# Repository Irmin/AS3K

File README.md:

# The Mechanical AlphaSmart 3000
This is a hardware mod for the AlphaSmart 3000 that swaps the keyboard out for a mechanical one.

The revisions here have compatibility issues and are deprecated. Information on the most recent revision is available [here](https://tilde.club/~jy4m/alphasmart).

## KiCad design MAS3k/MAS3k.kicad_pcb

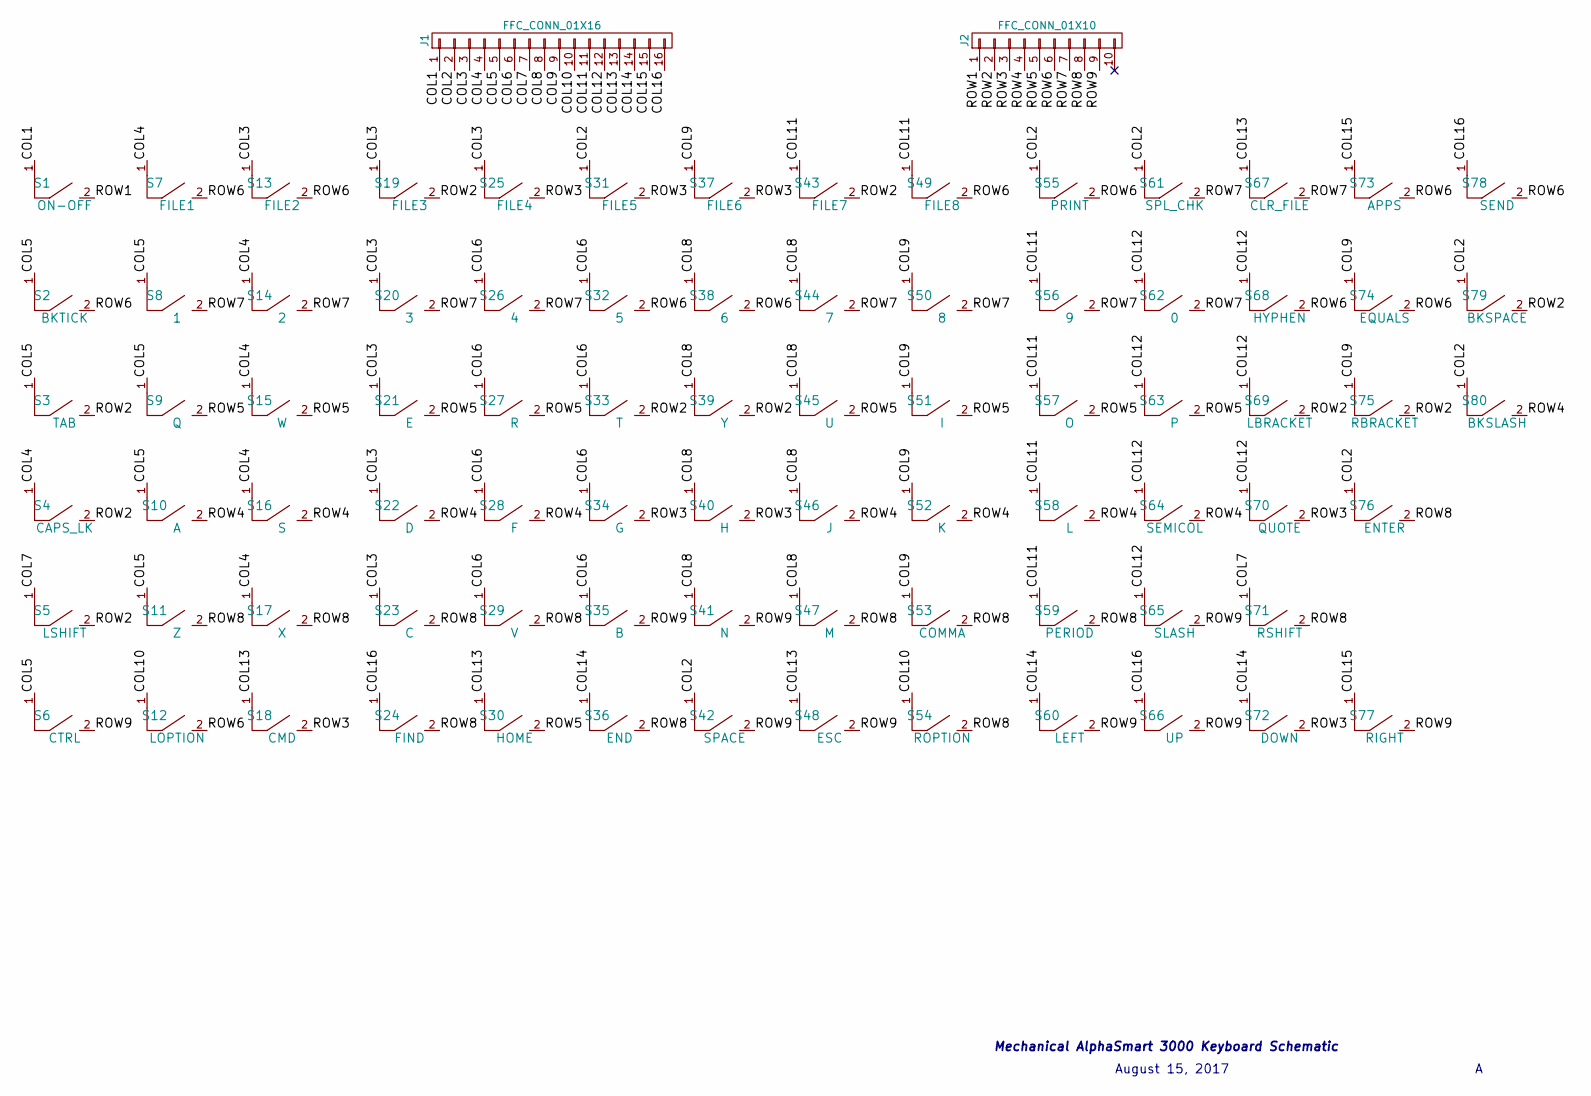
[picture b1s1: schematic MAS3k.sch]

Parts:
J1: FFC_CONN_01X16; SLW16R-1C7LF
J2: FFC_CONN_01X10; HLW10R-2C7LF
S1: ON-OFF; MX1A
S2: BKTICK; MX1A
S3: TAB; MX1A
S4: CAPS_LK; MX1A
S5: LSHIFT; MX1A
S6: CTRL; MX1A
S7: FILE1; MX1A
S8: 1; MX1A
S9: Q; MX1A
S10: A; MX1A
S11: Z; MX1A
S12: LOPTION; MX1A
S13: FILE2; MX1A
S14: 2; MX1A
S15: W; MX1A
S16: S; MX1A
S17: X; MX1A
S18: CMD; MX1A
S19: FILE3; MX1A
S20: 3; MX1A
S21: E; MX1A
S22: D; MX1A
S23: C; MX1A
S24: FIND; MX1A
S25: FILE4; MX1A
S26: 4; MX1A
S27: R; MX1A
S28: F; MX1A
S29: V; MX1A
S30: HOME; MX1A
S31: FILE5; MX1A
S32: 5; MX1A
S33: T; MX1A
S34: G; MX1A
S35: B; MX1A
S36: END; MX1A
S37: FILE6; MX1A
S38: 6; MX1A
S39: Y; MX1A
S40: H; MX1A
S41: N; MX1A
S42: SPACE; MX1A
S43: FILE7; MX1A
S44: 7; MX1A
S45: U; MX1A
S46: J; MX1A
S47: M; MX1A
S48: ESC; MX1A
S49: FILE8; MX1A
S50: 8; MX1A
S51: I; MX1A
S52: K; MX1A
S53: COMMA; MX1A
S54: ROPTION; MX1A
S55: PRINT; MX1A
S56: 9; MX1A
S57: O; MX1A
S58: L; MX1A
S59: PERIOD; MX1A
S60: LEFT; MX1A
S61: SPL_CHK; MX1A
S62: 0; MX1A
S63: P; MX1A
S64: SEMICOL; MX1A
S65: SLASH; MX1A
S66: UP; MX1A
S67: CLR_FILE; MX1A
S68: HYPHEN; MX1A
S69: LBRACKET; MX1A
S70: QUOTE; MX1A
S71: RSHIFT; MX1A
S72: DOWN; MX1A
S73: APPS; MX1A
S74: EQUALS; MX1A
S75: RBRACKET; MX1A
S76: ENTER; MX1A
S77: RIGHT; MX1A
S78: SEND; MX1A
S79: BKSPACE; MX1A
S80: BKSLASH; MX1A

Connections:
/COL1: J1.1, S1.1
/COL2: J1.2, S31.1, S42.1, S55.1, S61.1, S76.1, S79.1, S80.1
/COL3: J1.3, S13.1, S19.1, S20.1, S21.1, S22.1, S23.1, S25.1
/COL4: J1.4, S4.1, S7.1, S14.1, S15.1, S16.1, S17.1
/COL5: J1.5, S2.1, S3.1, S6.1, S8.1, S9.1, S10.1, S11.1
/COL6: J1.6, S26.1, S27.1, S28.1, S29.1, S32.1, S33.1, S34.1, S35.1
/COL7: J1.7, S5.1, S71.1
/COL8: J1.8, S38.1, S39.1, S40.1, S41.1, S44.1, S45.1, S46.1, S47.1
/COL9: J1.9, S37.1, S50.1, S51.1, S52.1, S53.1, S74.1, S75.1
/COL10: J1.10, S12.1, S54.1
/COL11: J1.11, S43.1, S49.1, S56.1, S57.1, S58.1, S59.1
/COL12: J1.12, S62.1, S63.1, S64.1, S65.1, S68.1, S69.1, S70.1
/COL13: J1.13, S18.1, S30.1, S48.1, S67.1
/COL14: J1.14, S36.1, S60.1, S72.1
/COL15: J1.15, S73.1, S77.1
/COL16: J1.16, S24.1, S66.1, S78.1
/ROW1: J2.1, S1.2
/ROW2: J2.2, S3.2, S4.2, S5.2, S19.2, S33.2, S39.2, S43.2, S69.2, S75.2, S79.2
/ROW3: J2.3, S18.2, S25.2, S31.2, S34.2, S37.2, S40.2, S70.2, S72.2
/ROW4: J2.4, S10.2, S16.2, S22.2, S28.2, S46.2, S52.2, S58.2, S64.2, S80.2
/ROW5: J2.5, S9.2, S15.2, S21.2, S27.2, S30.2, S45.2, S51.2, S57.2, S63.2
/ROW6: J2.6, S2.2, S7.2, S12.2, S13.2, S32.2, S38.2, S49.2, S55.2, S68.2, S73.2, S74.2, S78.2
/ROW7: J2.7, S8.2, S14.2, S20.2, S26.2, S44.2, S50.2, S56.2, S61.2, S62.2, S67.2
/ROW8: J2.8, S11.2, S17.2, S23.2, S24.2, S29.2, S36.2, S47.2, S53.2, S54.2, S59.2, S71.2, S76.2
/ROW9: J2.9, S6.2, S35.2, S41.2, S42.2, S48.2, S60.2, S65.2, S66.2, S77.2

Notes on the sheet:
Mechanical AlphaSmart 3000 Keyboard Schematic
August 15, 2017

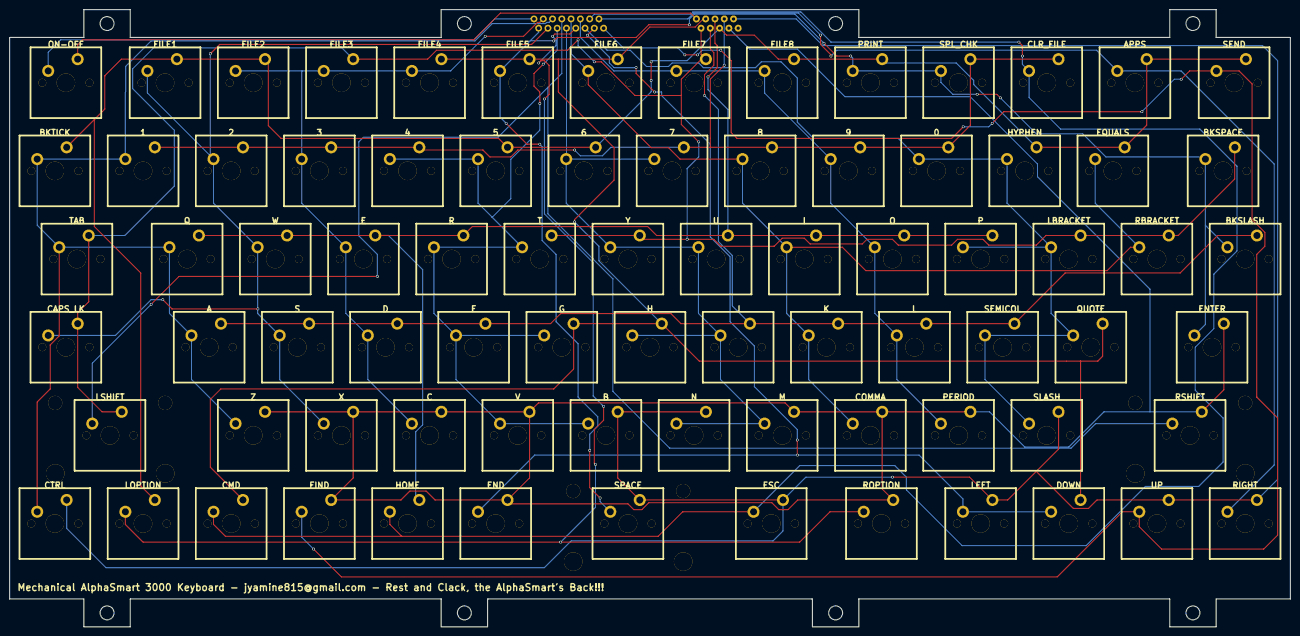
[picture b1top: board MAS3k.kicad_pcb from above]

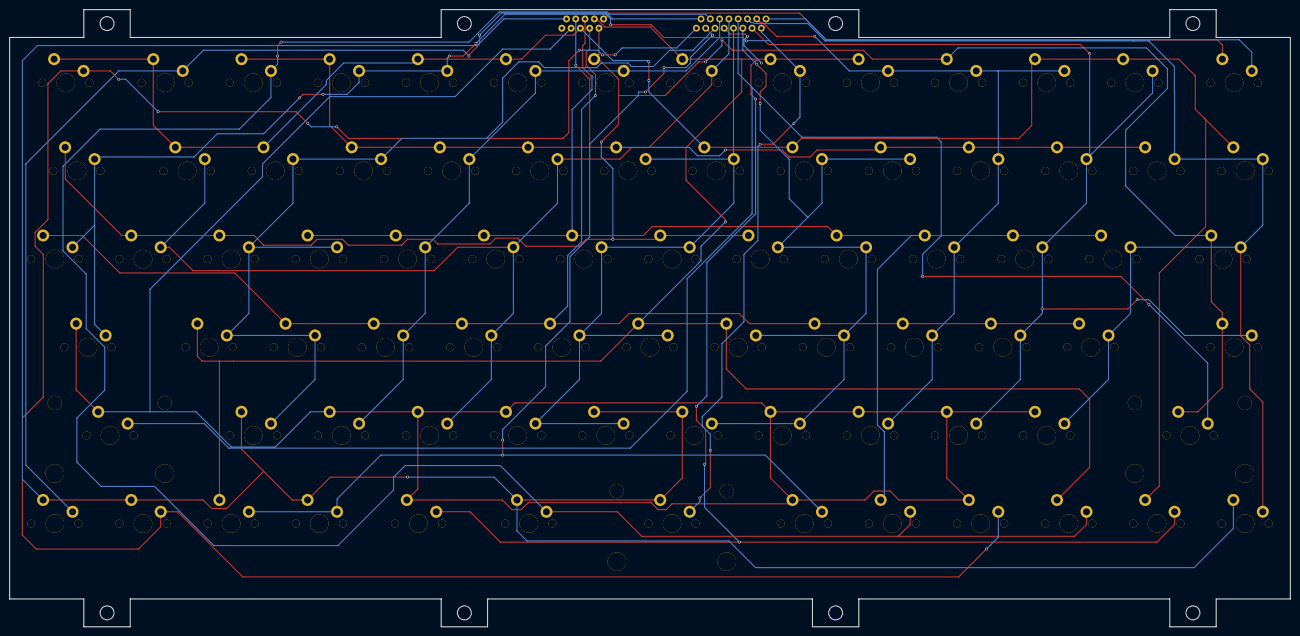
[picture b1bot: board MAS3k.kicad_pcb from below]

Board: 2 copper layers, 276.0 x 133.0 mm, 82 parts (2 on the bottom side), 25 nets.

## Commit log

2020-07-20 Updated README
    Linked the page on ~club and removed a link to the old Geekhack thread.
